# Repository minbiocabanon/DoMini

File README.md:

Domini
======

Mon projet domotique / My Home automation project

#ToDo

- trouver un moyen de ne pas mettre en dur les chemins dans les scripts de crontab ou certains scripts
- possibilité de mettre le chemin d'install du projet dans une variable puis d'utiliser cette variable dans les scripts pour travailler en relatif ?

#Demo
A l'adresse suivante, une version 'demo' de l'interface web de ma domotique est visible.
http://minbiocabanon.free.fr/static_domini/
*Attention : les actions (boutons) et certaines pages renverront des erreurs car il n'y a pas de base de données qui tourne pour la démo. Il s'agit uniquement d'une 'photo instantanée' de mes données et interface que je mets à jour régulièrement.*

#Intro
Architecture de l'installation :

#Captures d'écran / Screenshots

#Pré-requis
##Plateforme
Le serveur de la domotique est une machine Linux. 

Le projet ne nécessite que peu de ressources, jusqu'en aout 2014 il tournait sur un **Sheevaplug** :

- *Linux DEBIAN 6 Lenny*
- *ARM v5 1.2GHz*
- *RAM 512 Mo*
- *Flash 512 Mo* 
- *Lecteur SDCard (remplacé au bout de 6 mois par un disque dur USB car la SDCard ne supportait pas les nombreuses écritures)*
- *1 port USB*
- *1 port Ethernet*

Le projet Domini ayant atteint une certaine maturité et ayant acquis une place presque indispensable dans la maison (gestion du chauffage, volets et bientôt l'alarme) j'ai voulu fiabilisé le serveur.
Pour cela, j'ai migré du sheevaplug vers un **PC Barebone** (mon ancien PC recyclé) avec des disques dur montés en RAID1 et avec un peu plus de puissance pour réaliser les tâches (serveur web, sauvegarde base de données,...).

Voici les caractéristiques du PC (à titre d'information, cela n'indique pas le minimum nécessaire)

- *Linux DEBIAN 7*
- *PC x86 : Intel P4*
- *RAM : 2Go*
- *Disque dur : 2 x 80 Go ( montés en RAID1)*
- *1 port USB*
- *Wifi b/g/n*
- *Reseau Ethernet 10/100Mbps (optionnel une fois le wifi installé)*

#Paquets et logiciels
La liste des paquets installés sur ma machine est disponible sur le dépôt :

	~/serveur/systeme/dpkg.txt

Dans les grandes lignes voici ce qui est essentiel pour le projet :

- Serveur web : lighttpd
- Base de données : MySQL (sudo apt-get install mysql-server) , mot de passe superadmin : mysql
- PHP (sudo apt-get install php)
- serveur FTP : vsftp (pour récupération images des cameras IP),
- GCC (pour compiler les applications faites en C)
- GD (lib graphique pour HTML) , à confirmer
*Il existe certainement des dépendances ...*

Pour le développement, mise au point ou confort, j'utilise également :

- Samba
- Webmin
- Git (sudo apt-get install)
- screen

#Notes pour l'installation ou la migration vers un nouveau PC

## pb de boot sur ub1610 (perte de config?)
	si au reboot : Reboot and select proper boot device or Insert Boot Media in selected boot device and press any key
	vérifier la config dans le bios ,
	n'autoriser le boot que sur le disque SSD interne (pas sur le samsung de 256Go)
	désactiver les boot2, boot3 etc... ne conserver que le boot0 sur le disque flash interne

## activer ssh
	sudo systemctl start ssh
	
	#si ça ne marche pas, peut etre que openssh-server n'est pas installé, faire ceci :
		sudo apt-get remove --purge openssh-server
		sudo apt-get install openssh-server
		# puis retenter 
		sudo systemctl start ssh

## changer le nom des interfaces 
	# sur ub2004 , les noms des interfaces sont bizarres : enp1s0 pour ehternet,  wlp3s0 pour le wifi...

	Edit your /etc/default/grub changing the line from

	GRUB_CMDLINE_LINUX=""
	to

	GRUB_CMDLINE_LINUX="net.ifnames=0 biosdevname=0"
	and, finally run as root:

	$ sudo update-grub
	and reboot your system.

	$ sudo reboot

## network-manager
	# ajouter le paquet
	$ sudo apt install network-manager
	
	#ensuite utiliser l'interface graphique :
	$ nmtui
	
		## configuration wifi (manuelle et non persistante sera perdue au redémarrage , pas trouvé comment la rendre persistante. ajouter les infos dans /etc/network/interfaces ne fonctionne pas)

			# source : https://linuxcommando.blogspot.com/2013/10/how-to-connect-to-wpawpa2-wifi-network.html

				# activer l'interface wifi
			$sudo ip link set dev wlan0 up
			
				# lister les AP visibles
			$sudo iw dev wlan0 scan | less
			
				#This is a 2 step process. First, you generate a configuration file for wpa_supplicant that contains the pre-shared key ("passphrase") for the WiFi network.

			$ sudo -s
			[sudo] password for peter: 
			$ wpa_passphrase HADOPI-4G >> /etc/wpa_supplicant.conf 
			...type in the passphrase and hit enter...
			wpa_passphrase takes the SSID as the single argument. You must type in the passphrase for the WiFi network gorilla after you run the command. Using that information, wpa_passphrase will output the necessary configuration statements to the standard output. Those statements are appended to the wpa_supplicant configuration file located at /etc/wpa_supplicant.conf.

			#Note: you need root privilege to write to /etc/wpa_supplicant.conf.

			$ cat /etc/wpa_supplicant.conf 
				# reading passphrase from stdin
				#network={
				#	ssid="HADOPI-4G"
				#	#psk="mypassword"
				#	psk=keykeykeykeykeykeykeykeykeykeykeykeykeykey
				#}
				
				#The second step is to run wpa_supplicant with the new configuration file.
			
				# si besoin de stopper wpa_supplicant (à chaque fois qu'on lance wpa_supplicant, il y a une instance qui se lance et ça ne peut pas marche) : 
				# au cas, ou on tue les instances avant le lancer la suivante
			$sudo pkill wpa_supplicant
				
			$ sudo wpa_supplicant -B -D nl80211 -i wlan0 -c /etc/wpa_supplicant.conf
				# -B means run wpa_supplicant in the background.
				# -D specifies the wireless driver. wext is the generic driver.
				# -c specifies the path for the configuration file.
				# Use the iw command to verify that you are indeed connected to the SSID.
			
			# il peut y avoir problème avec l'argument de -D (nl80211 ou wext) , pour cela taper wpa_supplicant -h et regarder les options dispos :
				#[...]
				#drivers:
				#  nl80211 = Linux nl80211/cfg80211
				#  wext = Linux wireless extensions (generic)
				#  wired = Wired Ethernet driver
				#  macsec_linux = MACsec Ethernet driver for Linux
				#  none = no driver (RADIUS server/WPS ER)
				#[...]
			
			$ /sbin/iw wlan0 link
				#Connected to 00:1e:42:28:24:41 (on wlan0)
				#	SSID: HADOPI-4G
				#	freq: 2437
				#	RX: 7893 bytes (77 packets)
				#	TX: 697 bytes (6 packets)
				#	signal: -32 dBm
				#	rx bitrate: 1.0 MBit/s
				#	tx bitrate: 1.0 MBit/s

				#	bss flags:      short-preamble short-slot-time
				#	dtim period:    2
				#	beacon int:     100

				#Obtain IP address by DHCP
			$ sudo dhclient wlan0
				
			$ ip addr show wlan0
				#4: wlan0: <BROADCAST,MULTICAST,UP,LOWER_UP> mtu 1500 qdisc mq state UP group default qlen 1000
				#link/ether 00:21:6b:21:5c:1e brd ff:ff:ff:ff:ff:ff
				#inet 192.168.3.99/24 brd 192.168.3.255 scope global dynamic wlan0
				#   valid_lft 43168sec preferred_lft 43168sec
				#inet6 fe80::221:6bff:fe21:5c1e/64 scope link
				#   valid_lft forever preferred_lft forever
				
			# se connecter en ssh sur l'interface wlan0
			
				# eteindre l'ethernet
			$sudo ip link set eth0 down
				
				# changer la route
			$ sudo ip route del default
			$ sudo ip route add default via 192.168.3.1 dev wlan0	//192.168.3.1 : @ de la passerelle

				# tester la liaison à internet
			$ ping -I wlan0 8.8.8.8
				#PING 8.8.8.8 (8.8.8.8) from 192.168.3.99 wlan0: 56(84) bytes of data.
				#64 bytes from 8.8.8.8: icmp_seq=1 ttl=111 time=78.8 ms
				#64 bytes from 8.8.8.8: icmp_seq=2 ttl=111 time=55.2 ms
				#64 bytes from 8.8.8.8: icmp_seq=3 ttl=111 time=61.4 ms
				#^C
				#--- 8.8.8.8 ping statistics ---
				#3 packets transmitted, 3 received, 0% packet loss, time 2003ms
				#rtt min/avg/max/mdev = 55.243/65.150/78.831/9.992 ms

		!!!!!!!!!!!!!!!!!		# rendre 'persistant' cette configuration à chaque démarrage ?

## ngrok
	#ngrok permet d'établir une connexion à ub2004 à travers le routeur 4G (@ IP publique non routable !!!)
	
	$ ./ngrok http 80
	
	$ ./ngrok tcp 22
		#TCP tunnels are only available after you sign up.
		#Sign up at: https://ngrok.com/signup
		#If you have already signed up, make sure your authtoken is installed.
		#Your authtoken is available on your dashboard: https://dashboard.ngrok.com/auth/your-authtoken

		#ERR_NGROK_302

	# nécessite un enregistrement auprés du service ngrok
	# on retente avec le token communiqué aprés enregistrement
		
	$ ./ngrok authtoken <token>
	Authtoken saved to configuration file: /home/jcaulier/.ngrok2/ngrok.yml
	
	$ ./ngrok tcp 22
	
		#ngrok by @inconshreveable                                                                          (Ctrl+C to quit)

		#Session Status                online
		#Account                       minbiocabanon (Plan: Free)
		#Version                       2.3.35
		#Region                        United States (us)
		#Web Interface                 http://127.0.0.1:4040
		#Forwarding                    tcp://2.tcp.ngrok.io:17083 -> localhost:22

		#Connections                   ttl     opn     rt1     rt5     p50     p90
		#							  0       0       0.00    0.00    0.00    0.00

## byobu (remplace screen, déjà installé et avec de la couleur )
   F2 - Create a new window
   F3 - Move to previous window
   F4 - Move to next window
   F5 - Reload profile
   F6 - Detach from this session
   F7 - Enter copy/scrollback mode
   F8 - Re-title a window
   F9 - Configuration Menu
   F12 -  Lock this terminal
   shift-F2 - Split the screen horizontally
   ctrl-F2 - Split the screen vertically
   shift-F3 - Shift the focus to the previous split region
   shift-F4 - Shift the focus to the next split region
   shift-F5 - Join all splits
   ctrl-F6 - Remove this split
   ctrl-F5 - Reconnect GPG and SSH sockets
   shift-F6 - Detach, but do not logout
   alt-pgup - Enter scrollback mode
   alt-pgdn - Enter scrollback mode
   Ctrl-a $ - show detailed status
   Ctrl-a R - Reload profile
   Ctrl-a ! - Toggle key bindings on and off
   Ctrl-a k - Kill the current window
   Ctrl-a ~ - Save the current window's scrollback buffer

	   ## screen
		commande pour relancer un screen existant
			screen -r -d -h 1000000
			
		pour avoir une status bar , éditer .screenrc avec ces lignes
			caption always
			caption string "%{=b kg} [%n %t] %{=s ky}%W  %= %{=b}%H %{=s}%c "

		nécessite un redémarrage du pc (ou du service cron uniquement peut etre)

## GCC 
Installation :
	sudo apt install gcc
Installation lib mysql pour compiler sans erreur
	sudo apt-get install libmysqlclient-dev 

## Git
(rappel ici : https://git-scm.com/book/fr/v1/Les-bases-de-Git-D%C3%A9marrer-un-d%C3%A9p%C3%B4t-Git)
Rapatrier tout le projet
	se mettre dans ~src/ (ne pas créer de sous repertoire domini)
	git clone git://github.com/minbiocabanon/DoMini domini
	
Paramétrage du git
	git remote set-url origin https://github.com/minbiocabanon/DoMini
	git config --global user.email "minbiocabanon@gmail.com"
	git config --global user.name "minbiocabanon"

### serveur web : lighttpd

	# tuto qui a fonctionné pour ubuntu 20.04 : https://www.howtoforge.com/tutorial/how-to-install-lighttpd-with-php-fpm-and-mysql-on-ubuntu-2004/
	# alternative avec MariaDB : https://www.tecmint.com/install-lighttpd-in-ubuntu/
		# mariaDB : phpmyadmin fonctionne pareil
		# php7 : même syntaxe , donc rien à faire pour migrer
		# python : à vérifier !
	
installation :
	sudo apt-get install lighttpd
	
paramétrage lighttpd
	Changer dans /etc/lighttpd/lighttpd.conf le chemin  par défaut par /var/www/domini
	redémarre lighttpd : sudo /etc/init.d/lighttpd restart
	
	sudo lighty-enable-mod fastcgi 
	sudo lighty-enable-mod fastcgi-php
	sudo /etc/init.d/lighttpd force-reload

	attention aux droits pour lancer/arrêter lighttpd, il faut être root + admin
	Un truc : dès qu'on installe des extensions, il faut killer httpd et les fastcgi et les fpm
	Puis relancer lighttpd	

**ATTENTION** : certaines pages PHP lancent des executables (copiés dans www/domini/bin lors de la compilation). L'executable 'emitter' accède au port série /dev/ttyUSB0 pour transmettre les ordres au Jeelink. Il est possible que l'utilisateur www-data n'est pas la permission pour accéder au port série.

### PHP 7
	sudo apt-get install php
	sudo apt-get install php-gd
	
	# pour kitemeteo (php-curl)
	sudo apt install php-curl
	
##la commande suivante permet de donner accés en lecture/écriture à tous les groupes
	sudo chmod 666 /dev/ttyUSB0  # attention, à faire manuellement à chaque fois.
	
	# pour avoir les droits permanents ajouter le user au groupe dial
	sudo usermod -a -G dialout $user  # $user à remplacer par le user utilisant le port com en question

## INTERFACE WEB
	#Faire un lien symbolique de ~/serveur/www/domini vers /var/www/domini

	ln -s ~/src/domini/serveur/www/domini/ /var/www/domini

	#**ATTENTION** : il ne faut pas avoir créé /var/www/domini avant de créér le lien symbolique

	#Changer les droits, le propriétaire de /var/www/domini doit etre www-data

	sudo chown -R www-data:www-data ~/src/domini/serveur/www/domini
	
	# pour executer le script python pour gerer les volants roulant, celui-ci est lancé en tant que jcaulier dans une page PHP avec un 'sudo -u' . il faut autoriser www-data à faire cela avec visudo :
	
		#lancer
		sudo visudo
		
		# ajouter ces lignes à la fin :
		
			# www-data
			www-data ALL=(ALL) NOPASSWD: ALL

### SAMBA 
	# tuto : https://linuxconfig.org/how-to-configure-samba-server-share-on-ubuntu-20-04-focal-fossa-linux
	jcaulier@ub2004:~/src/domini/serveur/www/domini$ sudo useradd sambauser
	jcaulier@ub2004:~/src/domini/serveur/www/domini$ sudo smbpasswd -a sambauser
	New SMB password: samba
	Retype new SMB password: samba
	Added user sambauser.

### Webmin
Download deb package:
	wget sourceforge.net/projects/webadmin/files/webmin/2.013/webmin_2.013_all.deb
Install deb package on ubuntu system :
	sudo dpkg -i --force-depends webmin_2.013_all.deb
Install complete depedencies on ubuntu system :
	sudo apt-get install -f

After installation is completed, open your browser and user this link address https://localhost:10000/ to login webmin

Login as username is your ubuntu accout name and password account

Vous pouvez utiliser votre nom d'utilisateur courant et mot de passe, mais si vous voulez utiliser le compte "root" de webmin, celui-ci sera inaccessible car désactivé sur Ubuntu. Il faut par conséquent le changer en tapant :

	sudo /usr/share/webmin/changepass.pl /etc/webmin root votre_mot_de_passe

	Cette commande ne change pas le mot de passe « root » d'Ubuntu mais seulement celui de Webmin.
Redémarrer le service webmin :
	sudo service webmin restart

To remove all webmin system :
	sudo apt-get remove webmin	
	
### BOOTSTRAP
le framework [bootstrap](http://getbootstrap.com/) est utilisé pour la création des pages web.
Cela permet d'avoir une IHM 'responsive', c'est à dire qui s'adapte en fonction du support (PC, smartphone, tablette...).
Il existe pleins de plugins pour bootstrap afin de compléter l'ergonomie de l'interface web : boutons, slider, calendrier, curseurs ...

### HIGHSTOCK
J'ai utilisé [Highstock](http://www.highcharts.com/) pour générer les graphiques. basé sur du javascript, les graphiques sont bien faits et personnalisables à volonté.
	
## BASE DE DONNEES
la base de données tourne avec MySQL ou MariaDB.

Fichier contenant la structure de la base :

	~/serveur/bdd/struct_domotique.sql

créer la base:
	echo "create database domotique" | mysql -u root -p
	ou
	echo "create database domotique" | mariadb -u root -p
	
Fichier contenant l'exportation de toutes les données (non disponible sur le dépot git car du domaine privé)
L'importation de gros fichiers n'est pas possible via phpmyadmin, il faut utiliser mysql en ligne de commande:

 	mysql --user=root --password=mysql domotique < 	 ~/serveur/bdd/backup_domotique/backup-domotique.sql
	ou 
	mariadb --user=root --password=mysql domotique < 	 ~/serveur/bdd/backup_domotique/backup-domotique.sql
	
### phpmyadmin
	apt-get install phpmyadmin
	mdp : mysql

## SYSTEME
### Couleurs TERM
Pour avoir la console en couleur
	export TERM=xterm-color
	
### Accès au portCOM/USB
Le port ttyUSBx doit être utilisable par l'utilisateur www-data pour l'envoi de message directement depuis l'interface web.

	usermod -a -G dialout www-data
	ou
	adduser www-data dialout

Si vous lancez pyReceiver depuis votre compte user, ajoutez votre compte également de la même façon pour avoir le droit d'utiliser le port serie.

### rc.local
Afin de garantir le fonctionnement de la domotique en cas de redémarrage intempestif du serveur (si pas d'onduleur ou à la reprise du courant lorsque l'onduleur est sec), il convient d'appeler un script 'go.sh' qui contiendra les actions à lancer au démarrage.
En remplacement du rc.local qui pose des problèmes de droits et lors du portage/réinstallation, le go.sh est lancé par CRON qui se charge de le lancer au boot du système.

### Crontab:
Importer les taches CRON listées dans ce fichier :

	~/serveur/systeme/crontab.txt
	
Commande à éxécuter :

	crontab crontab.txt

### Users
L'utilisateur www-data doit disposer d'un mot de passe pour être compatible avec la configuration de mes caméras. Les caméras envoient par FTP des images dans le répertoire du serveur web.

Par défaut www-data ne possède pas de mot de passe. Lui donner "www-data" comme mot de passe à l'aide de la commande :

	sudo passwd www-data

### Connexions réseaux

Pour éviter que le wlan0 ne se déconnecte lorsque eth0 est débranché, dans /etc/network/interfaces , ne conserver 'auto' que devant le wlan0 (si wlan0) doit etre la liaison lan par défaut.
Configuration WEP pour interface wifi, voir ci-dessous.
	# cat /etc/network/interfaces
	
	# The loopback network interface
	#auto lo
	  iface lo inet loopback

	#auto eth0
	  iface eth0 inet dhcp

	auto wlan0
	  iface wlan0 inet dhcp
	   wireless-essid VIRUS
	   wireless-key s:"0000"

### resolv.conf
(pour résoudre pb de DNS si votre FAI est mauvais...)
installer le packet resolvconf

	sudo apt-get install resolvconf
	
éditer manuellement le fichier base :

	sudo nano /etc/resolvconf/resolv.conf.d/base
		
ajouter ces deux lignes :

	nameserver 208.67.222.222
	nameserver 208.67.220.220

sauver et relancer l'interface wifi/ethernet

	sudo /etc/init.d/networking restart

### client lftp
installer un client FTP light pour
	sudo apt install lftp
	
### Serveur vsFTP
installation :
	sudo apt-get install vsftpd

Ce serveur FTP doit être installé si vous avez installé tous les paquets présents dans le fichier ~/serveur/systeme/dpkg.txt

La configuration qui fonctionne (dans mon cas) est celle-ci :

fichier de configuration /etc/vsftpd.conf :

	listen=YES
	anonymous_enable=YES
	local_enable=YES
	write_enable=YES
	anon_upload_enable=YES
	anon_mkdir_write_enable=YES
	dirmessage_enable=YES
	xferlog_enable=YES
	connect_from_port_20=YES
	chown_uploads=YES
	chown_username=ftp
	ftpd_banner=Welcome to blah FTP service.
	secure_chroot_dir=/var/run/vsftpd
	pam_service_name=ftp			# BIEN VERIFIER CETTE LIGNE, sinon pb de login avec www-data pour les webcams
	rsa_cert_file=/etc/ssl/certs/vsftpd.pem
	anon_root=/var/www/	

## Logiciel
 - Modifier le fichier suivant pour y renseigner les identifiants de connexion à la base de données ainsi que le nom de la table:

	~/serveur/include/passwd.h (nommé passwd.h_ qu'il faut renommer)
	
 - Recompiler tous les logiciels directement sur la cible avec la commande 'make'

### cURL

Installer le paquet cURL pour PHP (optionnel)

	sudo apt-get install php5-curl

# Python
	## 2to3 , conversion sripts python2 en python3
		
		sudo apt install 2to3
		# exemple pour pyreceiver , option -w écrase le fichier source !
		2to3 pyreceiver.py -w
		
	## Pyserial
		http://pypi.python.org/pypi/pyserial

		télécharger le source, puis
			tar zxvf pyserial-3.2.1.tar.gz
			cd pyserial-3.2.1
			sudo python setup.py install
			
		lancer Python
			python

		importer serial
			>>>import serial
		
	## MariaDB Python
		# nécéssite d'installer pip3 pour python
		sudo apt-get update -y
		sudo apt install python3-pip
				
		sudo apt-get install -y libmariadb-dev
		pip3 install mariadb

	## MySQL Python  ---- Remplacé par MariaDB !!!!
		Installer le paquet :
			sudo apt-get install python-mysqldb

		Interpreteur PYTHON :

			>>> import MySQLdb as mdb
			>>> con = mdb.connect('localhost','root','mysql','domotique')
			>>> cur = con.cursor()
			>>> cur.execute("select version()")
			1L
			>>> ver = cur.fetchone()
			>>> print "%s" % ver
			5.5.40-0+wheezy1
		>>>
		
	##pushbullet python

		installer ez-python :
		télécharger ez-setup.py ici : https://pypi.python.org/pypi/setuptools	

			sudo python ez_setup.py

		Cloner le github pushbullet.py en local 
			mkdir ~/download/pypushbullet
			cd ~/download/pypushbullet
			git clone https://github.com/randomchars/pushbullet.py
			
		dans le répertoire , lancer :
			$ sudo python setup.py install

## Gestion onduleur USB (brouillon)

Voir dans le repertoire domini/serveur/ups pour plus d'info (readme.md)

liens utiles

https://doc.ubuntu-fr.org/nut

	$dmesg
	[ 4877.404023] usb 2-2: new low-speed USB device number 2 using uhci_hcd
	[ 4879.510653] usb 2-2: New USB device found, idVendor=0463, idProduct=ffff
	[ 4879.510659] usb 2-2: New USB device strings: Mfr=1, Product=2, SerialNumber=4
	[ 4879.510663] usb 2-2: Product: Protection Station
	[ 4879.510667] usb 2-2: Manufacturer: EATON
	[ 4879.510670] usb 2-2: SerialNumber: AN2E49008
	[ 4881.710163] generic-usb 0003:0463:FFFF.0004: hiddev0,hidraw2: USB HID v10.10 Device [EATON Protection Station] on usb-0000:00:1d.0-2/input0

##ddns
pour faire un ddns avec no-ip
	sudo curl -O https://www.noip.com/client/linux/noip-duc-linux.tar.gz
	sudo tar xzf noip-duc-linux.tar.gz
	cd noip-2.1.9-1/
	sudo make
	sudo make install
	#lancer le processus en fond de tâche
	sudo /usr/local/bin/noip2  #fonctionne pour le premier lancement
	sudo /usr/local/bin/noip2  -C #pour configurer un autre compte , il faudra arrêter le noip2

	# pour avoir le status du noip2 en cours :
	$sudo /usr/local/bin/noip2 -S
	1 noip2 process active.

	Process 26079, started as noip2, (version 2.1.9)
	Using configuration from /usr/local/etc/no-ip2.conf
	Last IP Address set 46.22.90.241
	Account ridezebigone@gmail.com
	configured for:
			host  kitemeteo.ddns.net
	Updating every 30 minutes via /dev/wlan0 with NAT enabled.
	
	# configuration pour 2 comptes
	$sudo /usr/local/bin/noip2 -C

	Auto configuration for Linux client of no-ip.com.

	Please enter the login/email string for no-ip.com  ridezebigone@gmail.com
	Please enter the password for user 'ridezebigone@gmail.com'  ************

	2 hosts are registered to this account.
	Do you wish to have them all updated?[N] (y/N)  y
	Please enter an update interval:[30]  30
	Do you wish to run something at successful update?[N] (y/N)  N

	New configuration file '/usr/local/etc/no-ip2.conf' created.

	# verification de l'activation des deux comptes no-ip
	$sudo /usr/local/bin/noip2 -S
	No noip2 processes active.

	Configuration data from /usr/local/etc/no-ip2.conf.
	Account ridezebigone@gmail.com
	configured for:
			host  kitemeteo.ddns.net
			host  mydomini.ddns.net
	Updating every 30 minutes via /dev/wlan0 with NAT enabled.
	
##videosurveillance
	#Memo
		Courte : 2.8 mm
			La caméra aura un angle de vue large mais avec une longueur de focale courte. La caméra prendra un grand angle de la zone par exemple à 180°, mais elle ne sera pas longue en profondeur. 

		Moyenne : 6 mm
			La caméra aura un angle de vue plus restreint que la focale courte et plus grande que la focale longue.

		Longue : 12 mm
			Ici l’angle de vue est très étroit mais la focal est très longue. Elle permet de surveiller une zone très lointaine mais très restreinte.

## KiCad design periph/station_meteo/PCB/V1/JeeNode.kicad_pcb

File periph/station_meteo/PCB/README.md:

Détails dans le wiki :

[https://github.com/RideZeBigOne/Domini/wiki/Periphs](https://github.com/RideZeBigOne/Domini/wiki/Periphs)

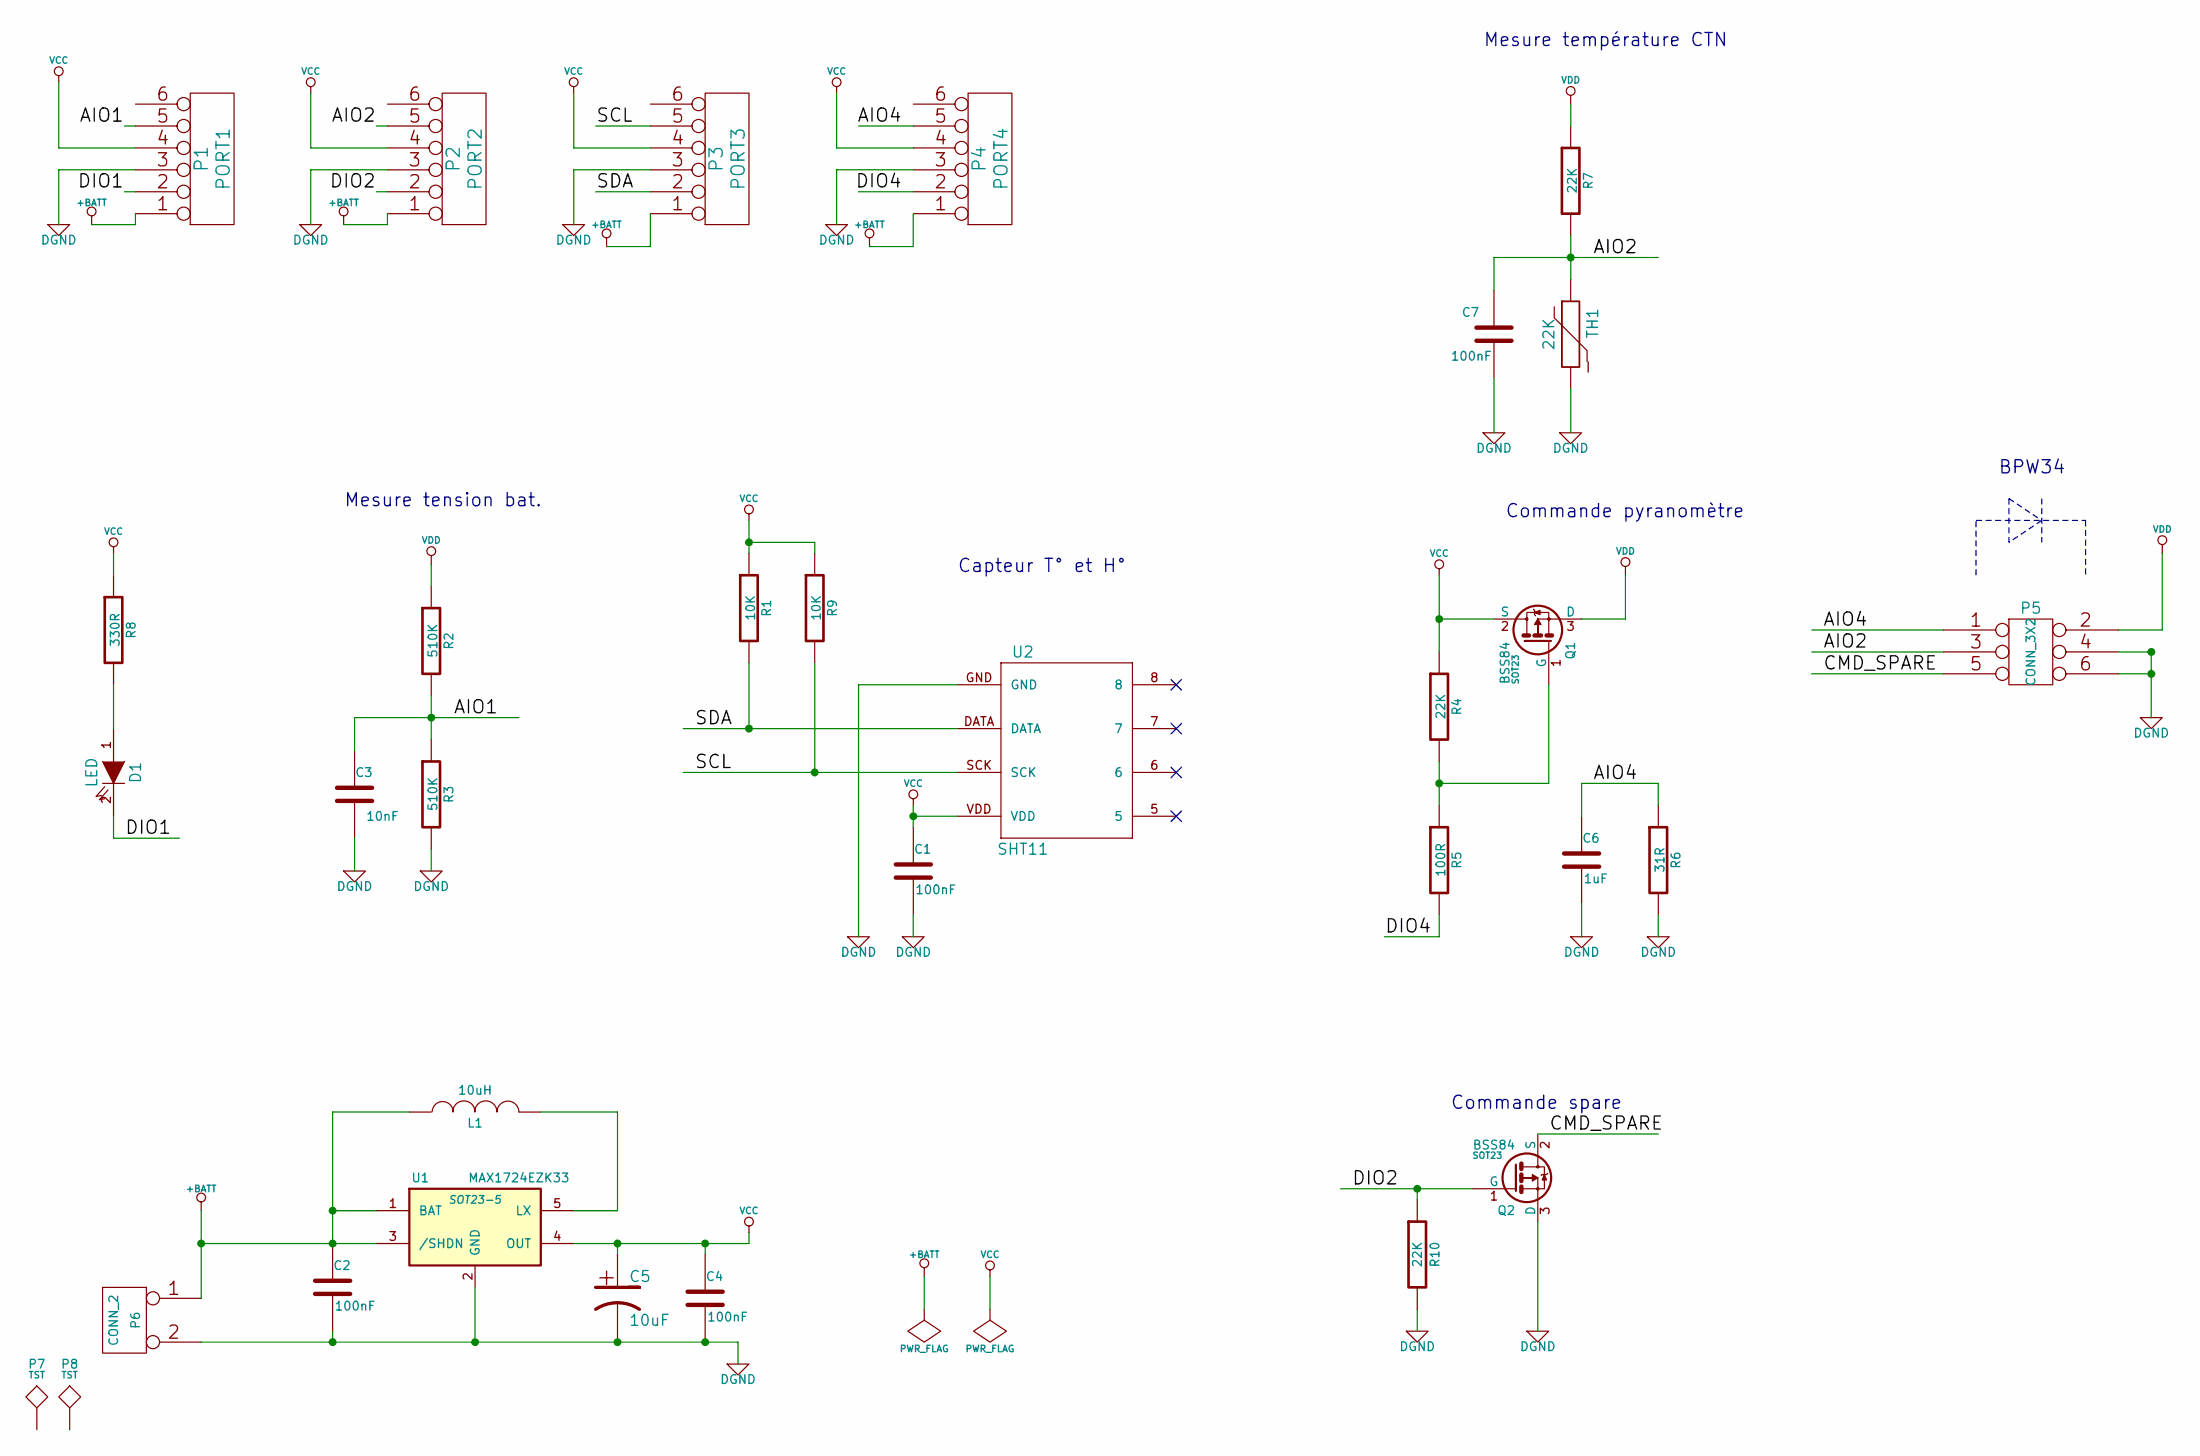
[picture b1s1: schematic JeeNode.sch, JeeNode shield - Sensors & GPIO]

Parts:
C1, C2, C4: 100nF; SM0805
C3: 10nF; SM1206
C5: 10uF; SM1206POL
C6: 1uF; SM1210L
C7: 100nF; SM1210L
D1: LED; LED-0805
L1: 10uH; SM1210
P1: PORT1; PIN_ARRAY-6X1
P2: PORT2; PIN_ARRAY-6X1
P3: PORT3; PIN_ARRAY-6X1
P4: PORT4; PIN_ARRAY-6X1
P5: CONN_3X2; pin_array_3x2
P6: CONN_2; PIN_ARRAY_2X1
P7, P8: TST; Hole_1mm
Q1, Q2: BSS84; SOT23
R1, R9: 10K; SM0805
R2, R3: 510K; SM0805
R4, R7, R10: 22K; SM0805
R5: 100R; SM0805
R6: 31R; SM0805
R8: 330R; SM0805
TH1: 22K; SM0805
U1: MAX1724EZK33; SOT23-5
U2: SHT11; sht11-SHT11

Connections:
+BATT: C2.1, L1.1, P1.1, P2.1, P3.1, P4.1, P6.1, U1.1 (BAT), U1.3 (/SHDN)
/AIO1: C3.1, P1.5, R2.2, R3.1
/AIO2: C7.1, P2.5, P5.3, R7.2, TH1.1
/AIO4: C6.1, P4.5, P5.1, R6.1
/CMD_SPARE: P5.5, Q2.2 (S)
/DIO1: D1.2 (K), P1.2
/DIO2: P2.2, Q2.1 (G), R10.1
/DIO4: P4.2, R5.2
/SCL: P3.5, R9.2, U2.SCK
/SDA: P3.2, R1.2, U2.DATA
DGND: C1.2, C2.2, C3.2, C4.2, C5.2, C6.2, C7.2, P1.3, P2.3, P3.3, P4.3, P5.4, P5.6, P6.2 (PM), Q2.3 (D), R3.2, R6.2, R10.2, TH1.2, U1.2 (GND), U2.GND
unnamed: Q1.1 (G), R4.2, R5.1
unnamed: L1.2, U1.5 (LX)
unnamed: D1.1 (A), R8.2
VCC: C1.1, C4.1, C5.1, P1.4, P2.4, P3.4, P4.4, Q1.2 (S), R1.1, R4.1, R8.1, R9.1, U1.4 (OUT), U2.VDD
VDD: P5.2, Q1.3 (D), R2.1, R7.1

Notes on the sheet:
Mesure tension bat.
Capteur T° et H°
Commande pyranomètre
Mesure température CTN
Commande spare
BPW34

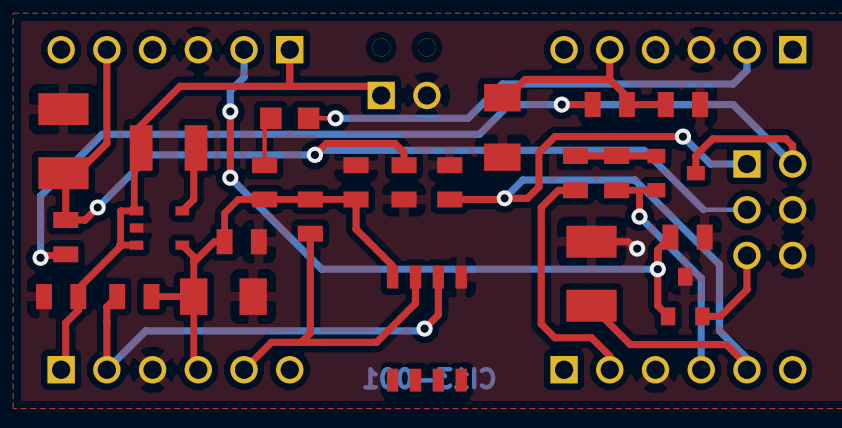
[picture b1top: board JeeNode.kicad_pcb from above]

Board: 2 copper layers, 32 parts (0 on the bottom side), 16 nets.

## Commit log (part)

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2014-08-02 Ajout lisez-moi.txt
2014-08-02 suppression lisez-moi.txt
2014-08-02 Ajout répertoire docs/ (commit repertoire par répertoire car pb de bande passante)
2014-08-02 ajout repertoire periph/ , contient les schemas, codes sources et docs concernant les modules jeenodes/arduino.
2014-08-04 ajout admin.php et mise a jour synoptiques
2014-08-04 suppression fichier passwd.h indesirable
2014-08-10 ajout screenshot de l'ihm web pour wiki/github
2014-08-12 modification des Makefile pour inclure un seul fichier password.h . ce .h contient les logins et password pour l'accea la bdd depuis les apapplis en C
2014-09-02 ajout test, log et graph de la connexion internet. mises � jour scripts
2014-09-02 ajout serveur/www/domini/php/highstock/csv_test_internet.php
2014-09-03 - Ajout info sur schéma électronique pour le brochage de la BPW34 (.sch et .pdf)
2014-09-04 correction test_internet.php, version precedente non valide
2014-09-20 test push et commit depuis X13
2014-10-11 - update jeenode sketche et schéma pour gérer la capteur à ultrason pour mesurer niveau de granulés dans le réservoir
2014-10-11 - update receiver.c pour gérer le message émis par le jeenode du poele : niveau dans le réservoir à granulés
2014-11-05 - correction sketche_poele/sketche_poele.ino : uniformisation timer pour gérer plusieurs évènements. Correction process pour mesure niveau granulés.
2014-11-05 - correction nom de la table pour le niveau de granulés
2014-11-05 - correction nom de fichier dans csv_pellet_rsv.php
2014-11-28 Gestion ultra sons dans reservoir pellets
2014-11-30 test changement config portCOM dans receiver. ajout internet.php
2014-11-30 modification Makefile pour utiliser le include generique
2014-12-02 - ajout README.md pour memo et notes diverses
2014-12-07 camera garage validee, changement de nom dans les pages web et scripts
2015-01-04 Ajout pyReceiver : gestion UART du Jeelink en Python ! et correction bug divers
2015-01-04 correction bug pyreceiver : manque un LF a la fin du message
2015-01-17 ftp.sh s a jour, ne fonctionnait plus depuis la migration sur le PC x86.
2015-01-21 changement page index , ajout vignettes camera a la plage de la meteo. changement des heures/jour pour uploard sur site miroir free. ajout creation de vignettes avec redim.php
2015-01-30 info rsv granules : change cm pour des pourcents pour la page index
2015-02-07 mise a jour README.md
2015-02-07 ajout de blindage dans pyreceiver : evite de planter si pas mysql pas dispo ou si port com occupe
2015-02-09 mise a jour suite gros bug qui avait face des scripts
2015-02-09 archivage structure bdd et crontab
2015-03-14 creation de script pour generer les csv de teleinfo complet dans le cas de la perte des csv( c'est arrive). amelioration de scripts divers.
2015-08-12 ajout script pour verif connexion wifi + cron
2015-10-10 update crontab and fix bug on pyreceiver
2015-10-18 ajout schéma principe dédié au poele
2015-12-02 fix typo
2015-12-13 Gestion des message $DBG , afin de mieux afficher les mesages de debug du jeelink
2015-12-31 pyreceiver : ajout gestion
2016-01-18 ajout fichier Log_batteries.txt pour mémoriser les dates de recharge des accus (à remplir manuellement)
2016-05-22 ajout gestion ACK
2016-06-04 ajout pyBypassPC en version python, la version en C sera supprimmee au prochain commit. correction de quelques bugs mineurs
2016-06-07 mise à jour photos bypass PC
2016-11-05 pygestionvr : misa jour
2016-11-28 - correction sur schematic et PCB de la station météo : erreur sur valeur de résistance et polarisation du pont diviseur pour la mesure de tension batterie
2016-11-30 correction bug sur effacement buffer : réalisé dans la boucle principal, prenait beaucoup de ressources CPU !
2016-12-01 migration interface web en PHP7 , possible bugs ou fichiers indesirables dans ce commit... nettoyage a faire prochainement
2016-12-01 mise en 'ignore' fichiers csv , temporairement pour éviter d'écraser les fichiers récents (migration de domini sur une nouvelle machine)
2016-12-01 correction bug dans restore_donnees_instant.php qd on est en mode manuel : les donnees affichees sur la page web etaient erronees. ajout lien symbolique pygestion_vr.pv dans www/domini/bin
2016-12-01 suppression serveur/www/domini/bin/gestion_vr , remplacear equivalent en python
2016-12-03 correction bug, un argument de trop dans requete mysql
2016-12-17 correction fichier php pour eviter les valeurs NULL dans les variables car mysql refusait la requete
2016-12-19 changement de droits des scripts
2016-12-19 remplacement de l'appel du binaire en C par l'equivalent en python
2017-01-07 mise à jour Synoptique_DoMini.odg , suppression mention sheeva plus et capacité du disque dur
2017-02-04 correction script graph et ftp
2017-02-04 mise a jour mais je ne sais pas quoi...
2017-02-04 recompilation de regul_temp.c sur nouvelle machine et correction de bug ou warning
2017-02-14 correction bug dans le script check wifi
2017-02-20 gestion de l'onduleur avec des scripts python, permet d'envoyer des messages via pushbullet. tentative de lancer le gestionnaire en tant que daemon
2017-02-22 ajout de log en bdd pour ups_daemonized
2017-02-23 mise a jour ups_daemonized.py
2017-02-25 amelioration du test serveur web dans la sentinelle
2017-02-27 conversion tri_bdd_edf en pytribdd_edf. amelioration du script qui permet de passer en arg une date de debut de nettoyage.
2017-03-01 ajout pytribdd.py pour usage de maintenance en cas de non fonctionnement des tache cron. si les tables n'ont pas ete nettoyees depuis un certain temps, il est possible de lancer manuellement le netto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
2017-03-01 correction bug sur OPTIMIZE TABLE
2017-03-01 mise a jour de README.md
2017-03-03 correction erreur dans message de debug
2017-03-04 suppression boite de dialoque qui ne servrait qu'au debug
2017-03-05 mise à jour screenshot IHM
2017-03-05 modif nom du fichier a generer
2017-03-06 correction bug sur requete pour l'heure de demarrage, empechant la creation de log a partir d'une table vide
2017-03-06 suppression menu meteo
2017-06-13 correction bug dans pygestion_vr.py : variable non declaree ajout de log pour la requete mysql envoyee
2017-09-28 mise a jour de la liste des paquets
2017-09-28 modification @ ip pour le test wifi
2017-10-19 ajout d'un tag time pour les images afin de contourner le cache du navigateur internet
2017-12-02 modif dans pytribdd.py , mais je ne sais plus quoi
2017-12-02 modif mineure sur regul_temp
2017-12-02 mise à jour du fichier README.md
2017-12-02 mise à jour des infos pour l'installation de UPS
2018-01-01 planning : correction makefile et adaptation a la nouvelle api mysql
2019-01-01 ajout de la suppression des infos de l'année précédente dans la table 'calendrier' sinon le logiciel planning n'arrivait pas à affecter aux lignes de l'année en cours, les infos de temperatures.
2019-01-01 correction bug dans le script de backup, il manquait le chemin d'execution. La recup des donnees de connexion ftp deplacee pour etre sur que la sauvegarde locale se fasse (en cas d'erreur ni, la sauv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
2019-01-01 ajout d'un critere pour tagger une ligne afin d'accelerer le processus : on tagge la ligne qui si elle n'est pas deja tagguee.
2019-01-02 ajout lancement daemon ups dans le go.sh , cela permet d'avoir la bdd rempli avec l'état de l'onduleur et les noticfications pushbullet
2019-01-02 correction mineure dans readme.md
2019-01-03 correction erreur de chemin pour le crontab. ajout du crontab à jour
2019-01-20 changement de camera dans le garage (une revotech de plus). scripts modifiés en conséquence. ajout d'une page kiwi.php qui servira de façon temporaire (ou pas)
2019-01-20 ajout d'un script de test pour pushbullet
2019-01-20 ajout fichier ups contenant les valeurs des variables dde l'onduleur
2019-01-26 changement de rep pour les images ext -> jardin
2019-01-27 mise a jour page reseau.php avec les nouvelles adresses IP
2019-01-27 correction bug sur timeoutnotif
2019-01-28 ajout myip dans page reseau
2019-07-26 correction bug dans pytribdd : il manquait un commit pour appliquer la suppression des lignes non taggees. du coup, la bdd ne faisait que grossir.
2019-07-26 ajout de la gestion du module de detection infrarouge PIR pour l'alarme... en mode TEST pour l'instant
2019-07-26 Ajout de la commande commit apres un delete dans mysql pour appliquer les modifs dans la bdd.
2019-11-13 correction condition de comparaison pour le niveau de granules dans le reservoir. enorme bug, comment ca a pu fonctionner avant ????
2019-11-14 correction bug dans la gestion des VR, cas degradé qui faisait planter sur un message de log et une variable non affectee
2019-12-01 Ajout d'un message de debug affichant le message envoye au poele
2020-02-12 sauvegarde bdd
2020-09-05 correction bug avec init pushbullet dans un try/except
2020-09-05 changement mineur pour voir les erreurs php dans index.php
2020-09-05 ajout d'une adresse supplémentaire dans les periph du reseau
2020-09-05 changement des noms pour les images webcams du garage
2020-12-08 ajout script pyCamClean qui permet de vider le cache de la galerie des images des cameras
2021-01-03 ajout d'info suite a installation sur nouvelle plateforme en ubuntu LTS 20.04 conversion en python3 des scripts
2021-01-16 daemon module included in python3 , useless now
2021-01-16 ups python scripts upgraded to python3
2021-01-16 shell commands upgraded to be compatible with ub2004
2021-01-16 recompile for ub2004 and new computer
2021-01-16 recompiled for ub2004 and new computer
2021-01-16 save database
2021-01-16 upgraded to python3 , mariadb and try to lauch pyreceiver if not running
2021-01-16 update package installed on computer
2021-01-16 bug fixed : month and year was hard coded!
2021-01-16 add some info about tty right needed
2021-01-30 forgot to change intervel for average solar flux. undo to 30 minute
2021-02-05 add debug message
2021-04-18 add some comments on sketche_teleinfo.ino remove some spoof lines on teleinfo_EDF.txt
2021-04-18 convert end of line to linux. change processthis default value to avoid python crash
2021-04-18 save dpkg list
2021-04-18 fix some http link for ip camera
2021-04-18 fix go.sh to able pyreceiver at startup after power outage
2021-04-18 ajout info sur ttyUSB0
2021-05-01 update crontab with boot task run pyreceiver
2021-05-01 change snapshot path : new camera
2021-05-15 save and archive sketche_teleinfo.ino before applying changes
2021-05-15 change camera settings
2021-05-15 save ngrok html redirection
2021-05-15 add a reminder about subscrition change (linky)
2021-05-15 log update
2021-07-28 maj lien ngrok
2021-07-28 correction GROS BUG git add serveur/pyReceiver/pyreceiver.pygit add serveur/pyReceiver/pyreceiver.py Fuite memoire à cause de la créatio de la session MariaDB dans les fonctions receiver() et emitter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
2021-08-07 mise à jour BDD
2021-11-22 mise a jour Readme de pytribdd
2021-11-22 sauvegarde architecture bdd
2021-11-22 sauvegarde liste des paquets
2021-12-06 mise à jour structure bdd et packages
2021-12-06 test gitkraken
    test puh gitkraken
2021-12-06 suppresion test gitkraken
2022-07-15 sauvegarde bdd et fichiers systeme
2022-08-14 sauvegarde bdd, structure bdd et package
2022-12-03 ajout démarrage service ups pour onduleur
2022-12-23 sauvegarde bdd et dpkg
2023-01-21 sauvegarde bdd et package
2023-01-21 changement de portCOM pour le JeeUSB
2023-02-25 optimisation : consigne manuelle sauvee dans PID afin de redemarrer en mode AUTO avec la même consigne que l'utilisateur. Evite de repartir avec la consigne parfois 0 ou 100 d'avant le passage en mod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
2023-09-15 update Sql archive, structure and packages
2024-01-02 ajout info sur planning dans fichier README
2024-01-02 correction bug : parametre change pour obtenir la date courante, l'annnee etait fausse !
2024-08-24 fix on pytribddel.py
2024-08-24 pyreceiver : update com PORT after moving server to new home
2024-08-24 update file and legend : 'comble' moved to 'garage'
2024-08-24 fix name series on garage graph
